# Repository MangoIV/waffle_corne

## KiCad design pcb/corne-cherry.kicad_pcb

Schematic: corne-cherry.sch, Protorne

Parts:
D1, D2, D3, D4, D5, D6, D7, D8, D9, D10, D11, D12, D13, D14, D15, D16, D17, D18, D19, D20, D21, D22, D23, D24, D25, D26, D27, D28, D29, D30, D31, D32, D33, D34, D35, D36, D37, D38, D39, D40, D41, D42: D; D3_SMD_v2; LCSC C402213
J1, J3: MJ-4PP-9; MJ-4PP-9_1side
J2, J4: OLED; OLED_1side
J5, J6: Conn_01x01_Male; PinHeader_1x01_P2.54mm_Vertical
J7: Conn_01x05; pimoroni-trackballl-bommod
JP1, JP2: SolderJumper_3_Open; SolderJumper-3_P1.3mm_Open_Pad1.0x1.5mm
LED1, LED2, LED3, LED4, LED5, LED6, LED7, LED8, LED9, LED10, LED11, LED12, LED13, LED14, LED15, LED16, LED17, LED18, LED19, LED20, LED21, LED22, LED23, LED24, LED25, LED26, LED27, LED28, LED29, LED30, LED31, LED32, LED33, LED34, LED35, LED36, LED37, LED38, LED39, LED40, LED41, LED42: YS-SK6812MINI-E
P1: Conn_01x03; PinSocket_1x03_P2.54mm_Vertical
P3: Conn_01x03; PinSocket_1x03_P2.54mm_Horizontal
R1, R2: 4.7k; R_0805_2012Metric
R3, R4: R_Small; Buzzer_Mallory_AST1109MLTRQ
RSW1, RSW2: SW_PUSH; ResetSW_1side
SW1, SW2, SW3, SW4, SW5, SW6, SW7, SW8, SW9, SW10, SW11, SW12, SW13, SW14, SW15, SW16, SW17, SW18, SW19, SW20, SW22, SW23, SW24, SW25, SW26, SW27, SW28, SW29, SW30, SW31, SW32, SW33, SW34, SW35, SW36, SW37, SW38, SW39, SW40, SW41: SW_PUSH; CherryMX_Hotswap
SW21, SW42: SW_PUSH; CherryMX_Hotswap_1.5u
SW43, SW44: Rotary_Encoder_Switch; RotaryEncoder_EC11-no-legs
U1, U2: ProMicro; ProMicro_v3

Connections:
B1_AUDIO: R3.1, U1.11
B1_AUDIO_R: R4.1, U2.11
ENC_A: SW43.A, U1.14
ENC_A_R: SW44.A, U2.14
ENC_B: SW43.B, U1.13
ENC_B_R: SW44.B, U2.13
GND: J1.C, J2.4, LED1.3, LED2.3, LED3.3, LED4.3, LED5.3, LED6.3, LED7.3, LED8.3, LED9.3, LED10.3, LED11.3, LED12.3, LED13.3, LED14.3, LED15.3, LED16.3, LED17.3, LED18.3, LED19.3, LED20.3, LED21.3, P1.1, RSW1.2, SW43.C, U1.3, U1.4, U1.23
GNDA: J3.C, J4.4, J7.1, LED22.3, LED23.3, LED24.3, LED25.3, LED26.3, LED27.3, LED28.3, LED29.3, LED30.3, LED31.3, LED32.3, LED33.3, LED34.3, LED35.3, LED36.3, LED37.3, LED38.3, LED39.3, LED40.3, LED41.3, LED42.3, P3.1, RSW2.2, SW44.C, U2.3, U2.4, U2.23
LED: JP1.1 (A), P1.3, U1.12
LED_r: JP2.1 (A), P3.3, U2.12
unnamed: D1.2 (A), SW1.2, SW43.S1
unnamed: D2.2 (A), SW2.2
unnamed: D3.2 (A), SW3.2
unnamed: D4.2 (A), SW4.2
unnamed: D5.2 (A), SW5.2
unnamed: D6.2 (A), SW6.2
unnamed: D7.2 (A), SW7.2
unnamed: D8.2 (A), SW8.2
unnamed: D9.2 (A), SW9.2
unnamed: D10.2 (A), SW10.2
unnamed: D11.2 (A), SW11.2
unnamed: D12.2 (A), SW12.2
unnamed: D13.2 (A), SW13.2
unnamed: D14.2 (A), SW14.2
unnamed: D15.2 (A), SW15.2
unnamed: D16.2 (A), SW16.2
unnamed: D17.2 (A), SW17.2
unnamed: D18.2 (A), SW18.2
unnamed: D19.2 (A), SW19.2
unnamed: D20.2 (A), SW20.2
unnamed: D21.2 (A), SW21.2
unnamed: D22.2 (A), SW22.2, SW44.S1
unnamed: D23.2 (A), SW23.2
unnamed: D24.2 (A), SW24.2
unnamed: D25.2 (A), SW25.2
unnamed: D26.2 (A), SW26.2
unnamed: D27.2 (A), SW27.2
unnamed: D28.2 (A), SW28.2
unnamed: D29.2 (A), SW29.2
unnamed: D30.2 (A), SW30.2
unnamed: D31.2 (A), SW31.2
unnamed: D32.2 (A), SW32.2
unnamed: D33.2 (A), SW33.2
unnamed: D34.2 (A), SW34.2
unnamed: D35.2 (A), SW35.2
unnamed: D36.2 (A), SW36.2
unnamed: D37.2 (A), SW37.2
unnamed: D38.2 (A), SW38.2
unnamed: D39.2 (A), SW39.2
unnamed: D40.2 (A), SW40.2
unnamed: D41.2 (A), SW41.2
unnamed: D42.2 (A), SW42.2
unnamed: J5.1, JP1.3 (B)
unnamed: J6.1, JP2.3 (B)
unnamed: JP1.2 (C), LED21.4
unnamed: JP2.2 (C), LED33.4
unnamed: LED1.2, LED4.4
unnamed: LED1.4, LED2.2
unnamed: LED2.4, LED5.2
unnamed: LED3.2, LED6.4
unnamed: LED4.2, LED7.4
unnamed: LED5.4, LED8.2
unnamed: LED6.2, LED9.4
unnamed: LED10.2, LED14.4
unnamed: LED7.2, LED10.4
unnamed: LED8.4, LED11.2
unnamed: LED11.4, LED15.2
unnamed: LED12.2, LED16.4
unnamed: LED9.2, LED12.4
unnamed: LED3.4, LED13.2
unnamed: LED13.4, LED17.2
unnamed: LED14.2, LED18.4
unnamed: LED15.4, LED19.2
unnamed: LED16.2, LED20.4
unnamed: LED17.4, LED21.2
unnamed: LED19.4, LED20.2
unnamed: LED22.2, LED26.4
unnamed: LED22.4, LED23.2
unnamed: LED23.4, LED27.2
unnamed: LED24.2, LED28.4
unnamed: LED24.4, LED25.2
unnamed: LED25.4, LED29.2
unnamed: LED26.2, LED30.4
unnamed: LED27.4, LED31.2
unnamed: LED28.2, LED32.4
unnamed: LED29.4, LED33.2
unnamed: LED30.2, LED34.4
unnamed: LED31.4, LED35.2
unnamed: LED32.2, LED36.4
unnamed: LED34.2, LED37.4
unnamed: LED35.4, LED38.2
unnamed: LED36.2, LED39.4
unnamed: LED37.2, LED40.4
unnamed: LED38.4, LED41.2
unnamed: LED39.2, LED42.4
unnamed: LED41.4, LED42.2
SCL: J2.2, U1.6
SCL_r: J4.2, J7.3, U2.6
SDA: J2.1, U1.5
SDA_r: J4.1, J7.4, U2.5
VCC: J1.D, J2.3, LED1.1, LED2.1, LED3.1, LED4.1, LED5.1, LED6.1, LED7.1, LED8.1, LED9.1, LED10.1, LED11.1, LED12.1, LED13.1, LED14.1, LED15.1, LED16.1, LED17.1, LED18.1, LED19.1, LED20.1, LED21.1, P1.2, R1.2, R3.2, U1.21
VDD: J3.D, J4.3, J7.5, LED22.1, LED23.1, LED24.1, LED25.1, LED26.1, LED27.1, LED28.1, LED29.1, LED30.1, LED31.1, LED32.1, LED33.1, LED34.1, LED35.1, LED36.1, LED37.1, LED38.1, LED39.1, LED40.1, LED41.1, LED42.1, P3.2, R2.2, R4.2, U2.21
col0: SW1.1, SW7.1, SW13.1, SW43.S2, U1.20
col0_r: SW22.1, SW28.1, SW34.1, SW44.S2, U2.20
col1: SW2.1, SW8.1, SW14.1, U1.19
col1_r: SW23.1, SW29.1, SW35.1, U2.19
col2: SW3.1, SW9.1, SW15.1, U1.18
col2_r: SW24.1, SW30.1, SW36.1, U2.18
col3: SW4.1, SW10.1, SW16.1, SW19.1, U1.17
col3_r: SW25.1, SW31.1, SW37.1, SW40.1, U2.17
col4: SW5.1, SW11.1, SW17.1, SW20.1, U1.16
col4_r: SW26.1, SW32.1, SW38.1, SW41.1, U2.16
col5: SW6.1, SW12.1, SW18.1, SW21.1, U1.15
col5_r: SW27.1, SW33.1, SW39.1, SW42.1, U2.15
data: J1.B, R1.1, U1.1
data_r: J3.B, R2.1, U2.1
reset: RSW1.1, U1.22
reset_r: RSW2.1, U2.22
row0: D1.1 (K), D2.1 (K), D3.1 (K), D4.1 (K), D5.1 (K), D6.1 (K), U1.7
row0_r: D22.1 (K), D23.1 (K), D24.1 (K), D25.1 (K), D26.1 (K), D27.1 (K), U2.7
row1: D7.1 (K), D8.1 (K), D9.1 (K), D10.1 (K), D11.1 (K), D12.1 (K), U1.8
row1_r: D28.1 (K), D29.1 (K), D30.1 (K), D31.1 (K), D32.1 (K), D33.1 (K), U2.8
row2: D13.1 (K), D14.1 (K), D15.1 (K), D16.1 (K), D17.1 (K), D18.1 (K), U1.9
row2_r: D34.1 (K), D35.1 (K), D36.1 (K), D37.1 (K), D38.1 (K), D39.1 (K), U2.9
row3: D19.1 (K), D20.1 (K), D21.1 (K), U1.10
row3_r: D40.1 (K), D41.1 (K), D42.1 (K), U2.10

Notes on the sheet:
Controllers
RGB
Switch Matrix
Misc

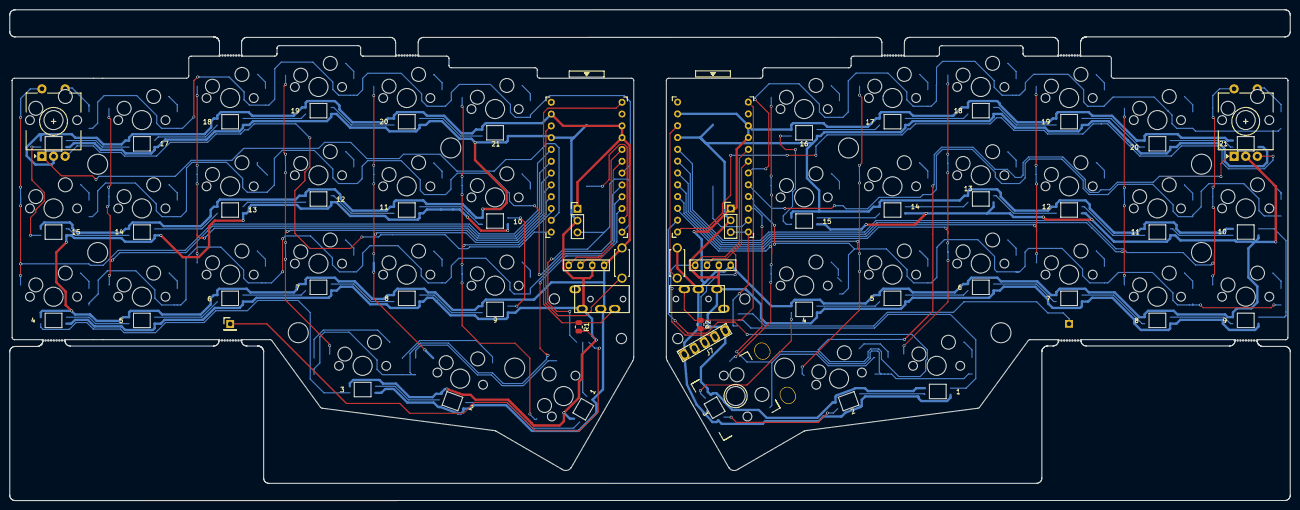
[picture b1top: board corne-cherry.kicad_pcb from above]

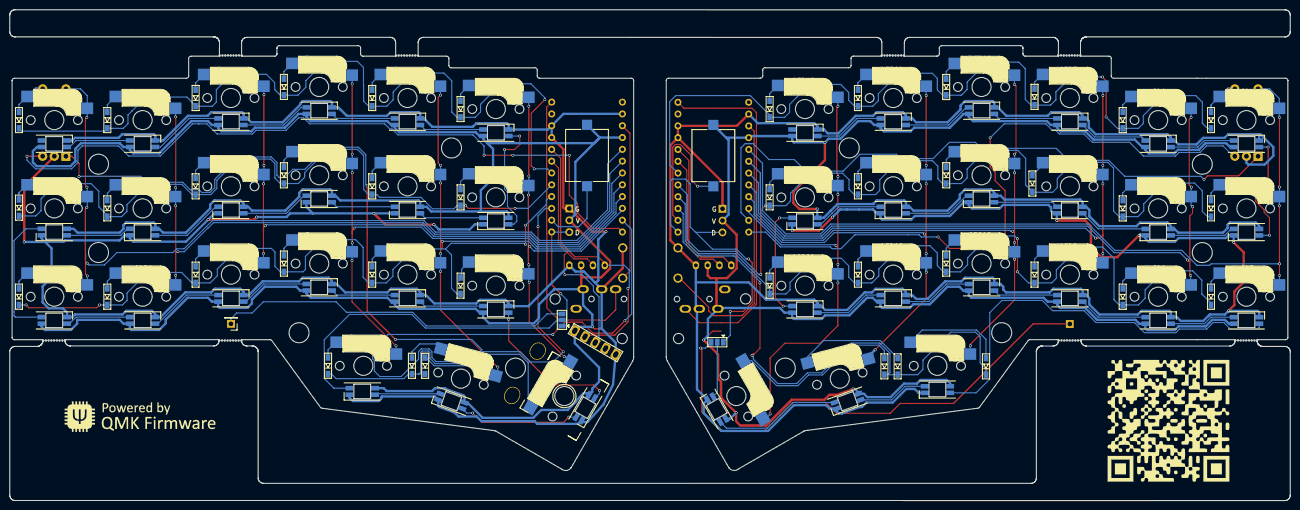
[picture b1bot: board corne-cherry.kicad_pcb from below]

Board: 2 copper layers, 275.5 x 105.6 mm, 161 parts (92 on the bottom side), 126 nets.

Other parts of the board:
Ref**: Val**; M2_HOLE_v2
Ref**#2, Ref**#3, Ref**#4, Ref**#5, Ref**#6, Ref**#7, Ref**#8, Ref**#9, Ref**#10, Ref**#11, Ref**#12, Ref**#13, Ref**#14: Val**; M2_HOLE_v2

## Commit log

2021-05-15 removed the weeb stuff to make a nice and clean pcb and regenreated gerbers
2021-05-15 added pimoroni
2021-05-15 added support for the pimoroni trackball and replotted the gerbers
